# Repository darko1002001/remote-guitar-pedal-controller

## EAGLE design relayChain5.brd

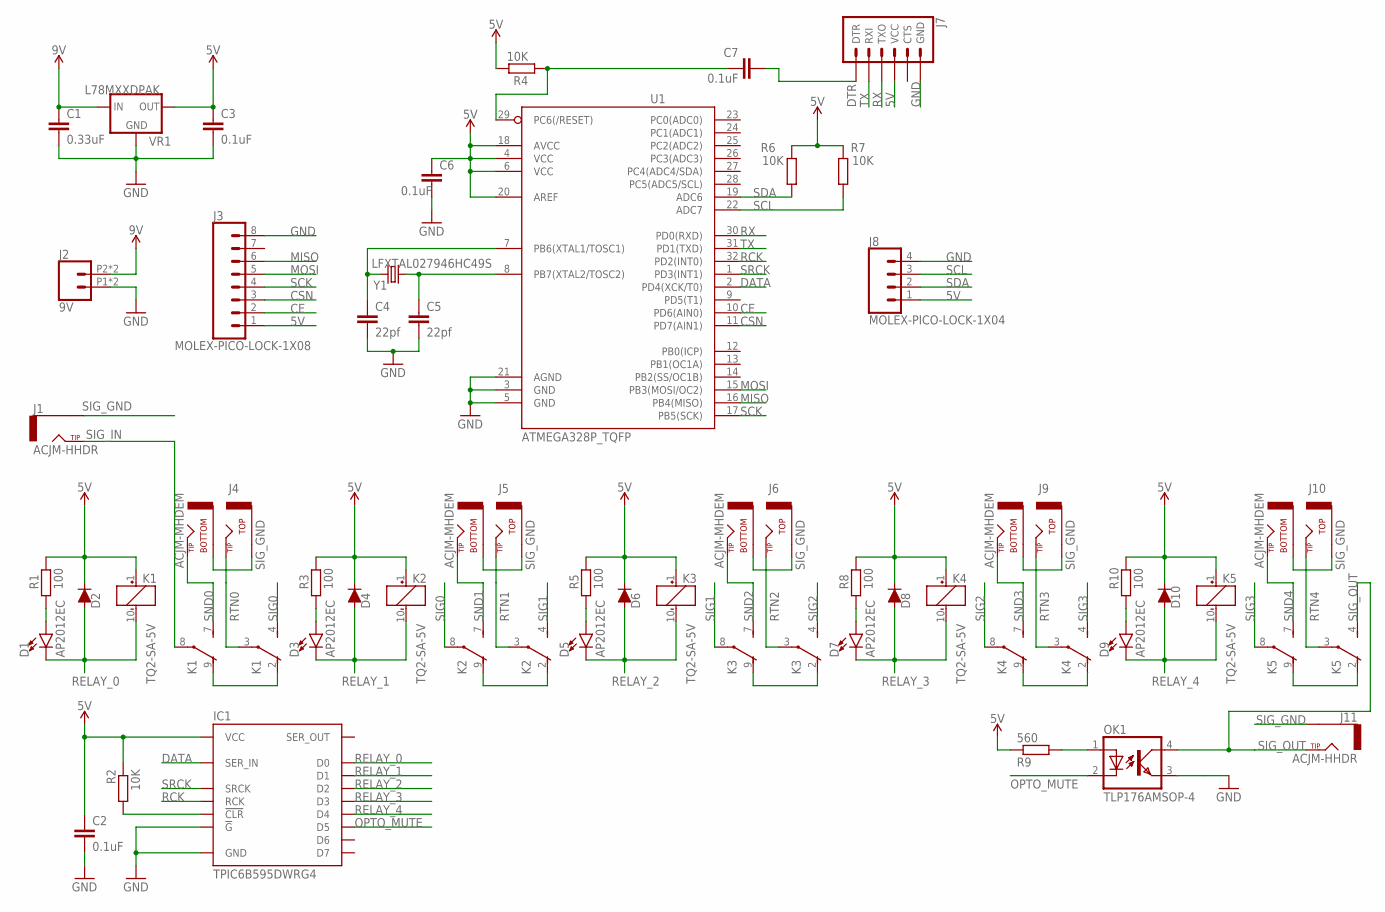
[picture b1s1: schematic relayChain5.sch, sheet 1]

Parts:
C1: 0.33uF; C0805
C2, C3, C6, C7: 0.1uF; C0805
C4, C5: 22pf; C0805
D1, D3, D5, D7, D9: AP2012EC; 0805-LED-AP2012EC
D2, D4, D6, D8, D10: 1n4148; SOD-123_MINI-SMA
IC1: TPIC6B595DWRG4; SOIC127P1032X265-20
J1, J11: ACJM-HHDR
J2: 9V; 1X02_POKEHOME
J3: MOLEX-PICO-LOCK-1X08
J4, J5, J6, J9, J10: ACJM-MHDEM
J7: 6_PIN_SERIAL_TARGETPTH-KIT; 1X06-KIT
J8: MOLEX-PICO-LOCK-1X04
K1, K2, K3, K4, K5: TQ2-SA-5V; TQ-SA
OK1: TLP176AMSOP-4; SOP254P715X220-4
R1, R3, R5, R8, R10: 100; M2012
R2: 10K; R0805
R4, R6, R7: 10K; M2012
R9: 560; R0805
U1: ATMEGA328P_TQFP; TQFP32-08
VR1: L78MXXDPAK; TO457P972X240-3
Y1: LFXTAL027946HC49S; XTAL1150X490X450

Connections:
5V: C2.1, C3.1, C6.1, D2.C, D4.C, D6.C, D8.C, D10.C, IC1.2 (VCC), J3.1, J7.4 (VCC), J8.1, K1.1 (+), K2.1 (+), K3.1 (+), K4.1 (+), K5.1 (+), R1.2, R2.1, R3.2, R4.2, R5.2, R6.1, R7.1, R8.2, R9.1, R10.2, U1.4 (VCC), U1.6 (VCC), U1.18 (AVCC), U1.20 (AREF), VR1.2 (OUT)
9V: C1.1, J2.P2 (2), J2.P4 (2), VR1.1 (IN)
CE: J3.2, U1.10 (PD6(AIN0))
CSN: J3.3, U1.11 (PD7(AIN1))
DATA: IC1.3 (SER_IN), U1.2 (PD4(XCK/T0))
DTR: C7.2, J7.1 (DTR)
GND: C1.2, C2.2, C3.2, C4.2, C5.2, C6.2, IC1.9 (!G), IC1.10 (GND), IC1.11 (GND), IC1.19 (GND), J2.P1 (1), J2.P3 (1), J3.8, J7.6 (GND), J8.4, OK1.3 (EMIT), U1.3 (GND), U1.5 (GND), U1.21 (AGND), VR1.3 (GND)
MISO: J3.6, U1.16 (PB4(MISO))
MOSI: J3.5, U1.15 (PB3(MOSI/OC2))
unnamed: K1.2 (O), K1.9 (O)
unnamed: IC1.8 (!CLR), R2.2
unnamed: D1.A, R1.1
unnamed: K2.2 (O), K2.9 (O)
unnamed: D3.A, R3.1
unnamed: K3.2 (O), K3.9 (O)
unnamed: D5.A, R5.1
unnamed: K4.2 (O), K4.9 (O)
unnamed: D7.A, R8.1
unnamed: K5.2 (O), K5.9 (O)
unnamed: D9.A, R10.1
unnamed: OK1.1 (A), R9.2
unnamed: C4.1, U1.7 (PB6(XTAL1/TOSC1)), Y1.1
unnamed: C5.1, U1.8 (PB7(XTAL2/TOSC2)), Y1.2
unnamed: C7.1, R4.1, U1.29 (PC6(/RESET))
OPTO_MUTE: IC1.15 (D5), OK1.2 (C)
RCK: IC1.12 (RCK), U1.32 (PD2(INT0))
RELAY_0: D1.C, D2.A, IC1.4 (D0), K1.10 (-)
RELAY_1: D3.C, D4.A, IC1.5 (D1), K2.10 (-)
RELAY_2: D5.C, D6.A, IC1.6 (D2), K3.10 (-)
RELAY_3: D7.C, D8.A, IC1.7 (D3), K4.10 (-)
RELAY_4: D9.C, D10.A, IC1.14 (D4), K5.10 (-)
RTN0: J4.9 (TIP_TOP), J4.12 (TIP_TOP), K1.3
RTN1: J5.9 (TIP_TOP), J5.12 (TIP_TOP), K2.3
RTN2: J6.9 (TIP_TOP), J6.12 (TIP_TOP), K3.3
RTN3: J9.9 (TIP_TOP), J9.12 (TIP_TOP), K4.3
RTN4: J10.9 (TIP_TOP), J10.12 (TIP_TOP), K5.3
RX: J7.3 (TXO), U1.30 (PD0(RXD))
SCK: J3.4, U1.17 (PB5(SCK))
SCL: J8.3, R7.2, U1.22 (ADC7)
SDA: J8.2, R6.2, U1.19 (ADC6)
SIG0: K1.4 (S), K2.8
SIG1: K2.4 (S), K3.8
SIG2: K3.4 (S), K4.8
SIG3: K4.4 (S), K5.8
SIG_GND: J1.SLEEVE_1 (SLEEVE), J1.SLEEVE_2 (SLEEVE), J4.1 (SLEEVE_BOTTOM), J4.4 (SLEEVE_BOTTOM), J4.7 (SLEEVE_TOP), J4.10 (SLEEVE_TOP), J5.1 (SLEEVE_BOTTOM), J5.4 (SLEEVE_BOTTOM), J5.7 (SLEEVE_TOP), J5.10 (SLEEVE_TOP), J6.1 (SLEEVE_BOTTOM), J6.4 (SLEEVE_BOTTOM), J6.7 (SLEEVE_TOP), J6.10 (SLEEVE_TOP), J9.1 (SLEEVE_BOTTOM), J9.4 (SLEEVE_BOTTOM), J9.7 (SLEEVE_TOP), J9.10 (SLEEVE_TOP), J10.1 (SLEEVE_BOTTOM), J10.4 (SLEEVE_BOTTOM), J10.7 (SLEEVE_TOP), J10.10 (SLEEVE_TOP), J11.SLEEVE_1 (SLEEVE), J11.SLEEVE_2 (SLEEVE)
SIG_IN: J1.TIP_1 (TIP), J1.TIP_2 (TIP), K1.8
SIG_OUT: J11.TIP_1 (TIP), J11.TIP_2 (TIP), K5.4 (S), OK1.4 (COL)
SND0: J4.3 (TIP_BOTTOM), J4.6 (TIP_BOTTOM), K1.7 (S)
SND1: J5.3 (TIP_BOTTOM), J5.6 (TIP_BOTTOM), K2.7 (S)
SND2: J6.3 (TIP_BOTTOM), J6.6 (TIP_BOTTOM), K3.7 (S)
SND3: J9.3 (TIP_BOTTOM), J9.6 (TIP_BOTTOM), K4.7 (S)
SND4: J10.3 (TIP_BOTTOM), J10.6 (TIP_BOTTOM), K5.7 (S)
SRCK: IC1.13 (SRCK), U1.1 (PD3(INT1))
TX: J7.2 (RXI), U1.31 (PD1(TXD))

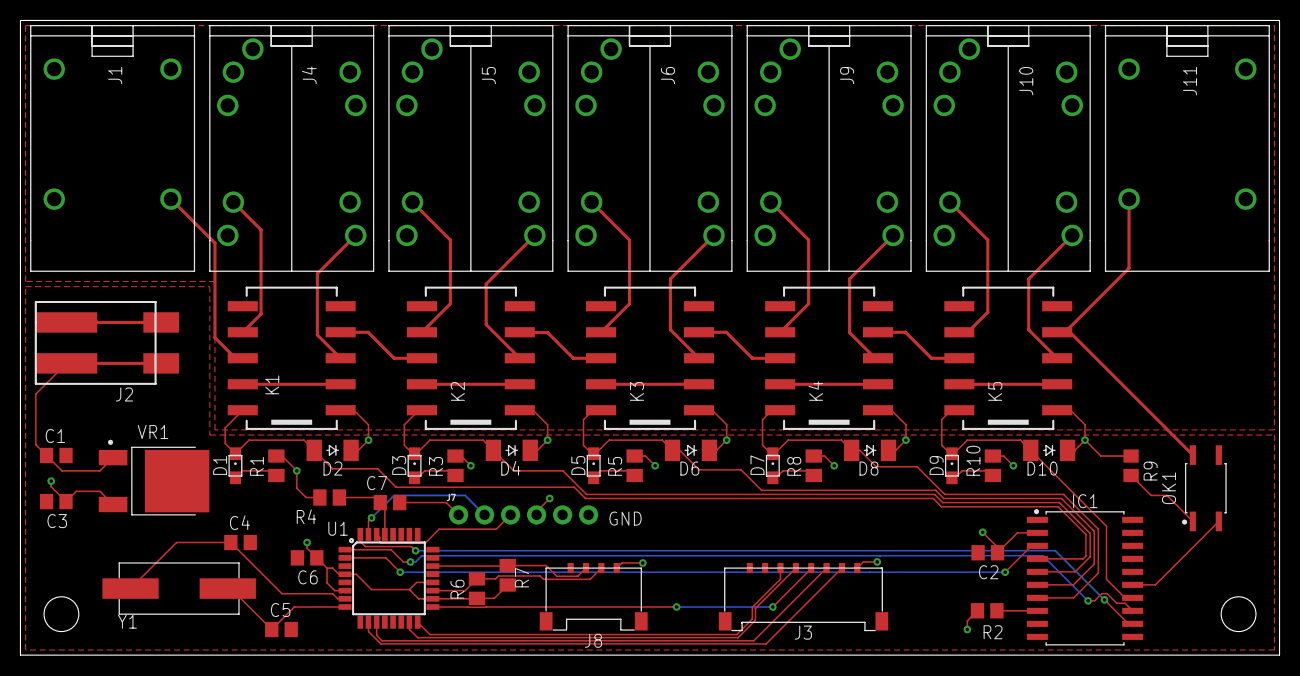
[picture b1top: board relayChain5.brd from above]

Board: 2 copper layers, 123.0 x 62.0 mm, 48 parts (0 on the bottom side), 54 nets.

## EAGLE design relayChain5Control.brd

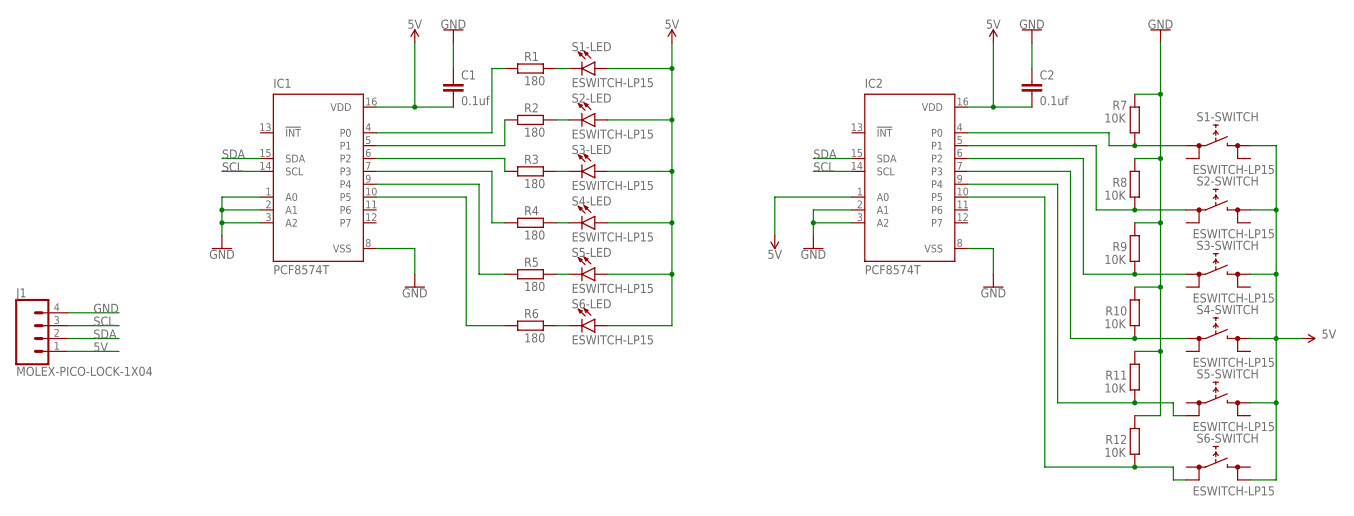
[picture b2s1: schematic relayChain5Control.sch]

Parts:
C1, C2: 0.1uf; C0805
IC1, IC2: PCF8574T; SO16W
J1: MOLEX-PICO-LOCK-1X04
R1, R2, R3, R4, R5, R6: 180; R2012
R7, R8, R9, R10, R11, R12: 10K; R2012
S1, S2, S3, S4, S5, S6: ESWITCH-LP15

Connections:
5V: C1.2, C2.2, IC1.16 (VDD), IC2.1 (A0), IC2.16 (VDD), J1.1, S1.P$3 (1), S1.P$5 (A), S2.P$3 (1), S2.P$5 (A), S3.P$3 (1), S3.P$5 (A), S4.P$3 (1), S4.P$5 (A), S5.P$3 (1), S5.P$5 (A), S6.P$4 (1), S6.P$5 (A)
GND: C1.1, C2.1, IC1.1 (A0), IC1.2 (A1), IC1.3 (A2), IC1.8 (VSS), IC2.2 (A1), IC2.3 (A2), IC2.8 (VSS), J1.4, R7.2, R8.2, R9.2, R10.2, R11.2, R12.2
unnamed: IC1.4 (P0), R1.1
unnamed: R1.2, S1.P$6 (C)
unnamed: IC1.5 (P1), R2.1
unnamed: IC1.6 (P2), R3.1
unnamed: IC2.4 (P0), R7.1, S1.P$1 (0)
unnamed: IC2.5 (P1), R8.1, S2.P$1 (0)
unnamed: R2.2, S2.P$6 (C)
unnamed: IC2.6 (P2), R9.1, S3.P$1 (0)
unnamed: IC2.7 (P3), R10.1, S4.P$1 (0)
unnamed: IC2.9 (P4), R11.1, S5.P$2 (0)
unnamed: IC1.7 (P3), R4.1
unnamed: IC1.9 (P4), R5.1
unnamed: R3.2, S3.P$6 (C)
unnamed: IC2.10 (P5), R12.1, S6.P$2 (0)
unnamed: R4.2, S4.P$6 (C)
unnamed: R5.2, S5.P$6 (C)
unnamed: R6.2, S6.P$6 (C)
unnamed: IC1.10 (P5), R6.1
SCL: IC1.14 (SCL), IC2.14 (SCL), J1.3
SDA: IC1.15 (SDA), IC2.15 (SDA), J1.2

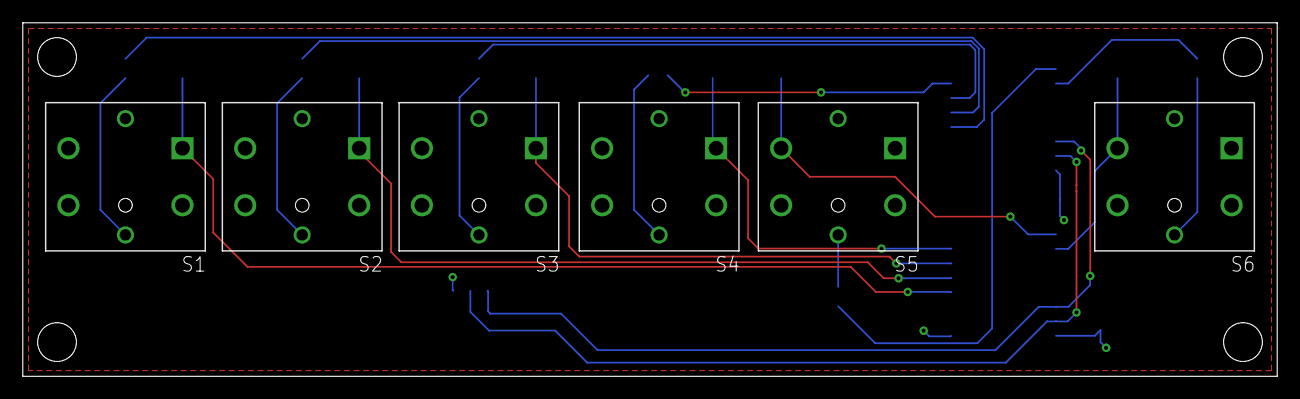
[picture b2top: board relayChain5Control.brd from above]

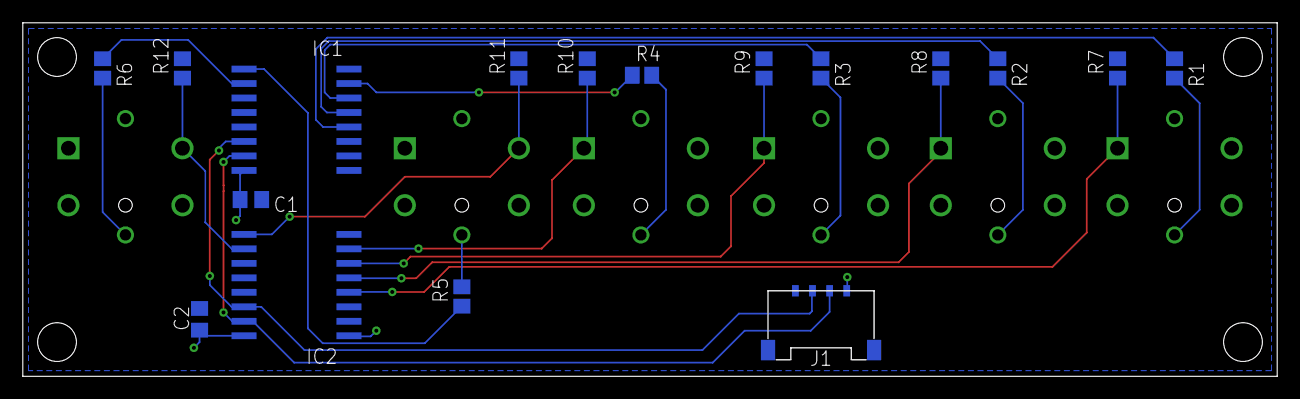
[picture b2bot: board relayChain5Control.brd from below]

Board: 2 copper layers, 110.0 x 31.0 mm, 23 parts (17 on the bottom side), 22 nets.

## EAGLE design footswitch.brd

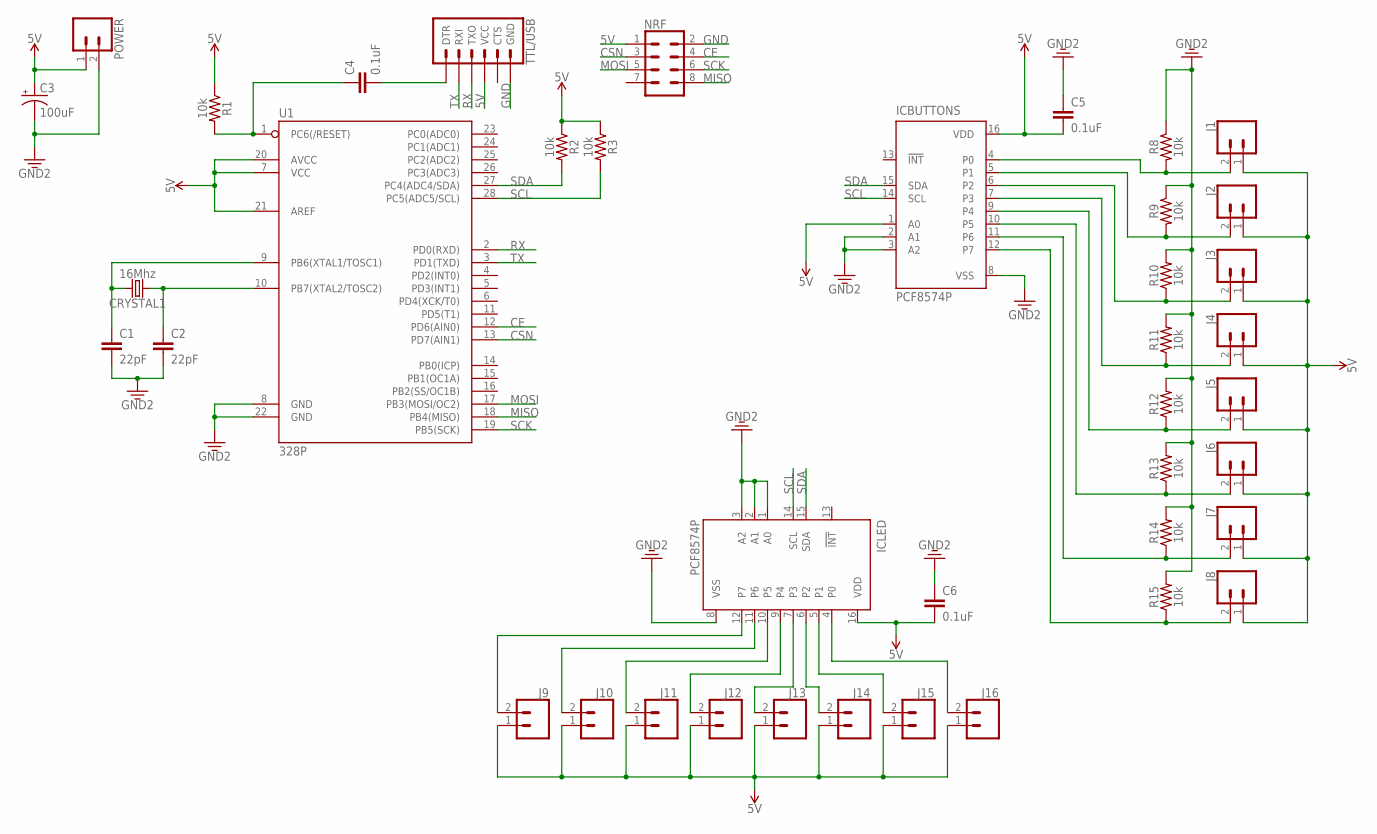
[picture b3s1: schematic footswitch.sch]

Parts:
C1, C2: 22pF; CAP-PTH-2.54
C3: 100uF; CPOL-RADIAL-2.5MM-6.5MM
C4, C5, C6: 0.1uF; CAP-PTH-SMALL-KIT
CRYSTAL1: 16Mhz; HC49US
ICBUTTONS: PCF8574P; DIL16
ICLED: PCF8574P; DIL16
J1, J2, J3, J4, J5, J6, J7, J8, J9, J10, J11, J12, J13, J14, J15, J16: CONN_02POLAR; MOLEX-1X2
NRF: CONN_04X2; 2X4
POWER: CONN_02; 1X02
R1, R2, R3, R8, R9, R10, R11, R12, R13, R14, R15: 10k; AXIAL-0.3
TTL/USB: 6_PIN_SERIAL_TARGETPTH-KIT; 1X06-KIT
U1: 328P; DIP28

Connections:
5V: C3.1 (+), C5.2, C6.2, ICBUTTONS.1 (A0), ICBUTTONS.16 (VDD), ICLED.16 (VDD), J1.1, J2.1, J3.1, J4.1, J5.1, J6.1, J7.1, J8.1, J9.1, J10.1, J11.1, J12.1, J13.1, J14.1, J15.1, J16.1, NRF.1, POWER.1, R1.P$1 (1), R2.P$1 (1), R3.P$1 (1), TTL/USB.4 (VCC), U1.7 (VCC), U1.20 (AVCC), U1.21 (AREF)
CE: NRF.4, U1.12 (PD6(AIN0))
CSN: NRF.3, U1.13 (PD7(AIN1))
GND: C1.2, C2.2, C3.2 (-), C5.1, C6.1, ICBUTTONS.2 (A1), ICBUTTONS.3 (A2), ICBUTTONS.8 (VSS), ICLED.1 (A0), ICLED.2 (A1), ICLED.3 (A2), ICLED.8 (VSS), NRF.2, POWER.2, R8.P$1 (1), R9.P$1 (1), R10.P$2 (2), R11.P$2 (2), R12.P$2 (2), R13.P$2 (2), R14.P$2 (2), R15.P$2 (2), TTL/USB.6 (GND), U1.8 (GND), U1.22 (GND)
MISO: NRF.8, U1.18 (PB4(MISO))
MOSI: NRF.5, U1.17 (PB3(MOSI/OC2))
unnamed: C4.1, R1.P$2 (2), U1.1 (PC6(/RESET))
unnamed: C1.1, CRYSTAL1.2, U1.9 (PB6(XTAL1/TOSC1))
unnamed: C2.1, CRYSTAL1.1, U1.10 (PB7(XTAL2/TOSC2))
unnamed: C4.2, TTL/USB.1 (DTR)
unnamed: ICBUTTONS.4 (P0), J1.2, R8.P$2 (2)
unnamed: ICBUTTONS.5 (P1), J2.2, R9.P$2 (2)
unnamed: ICLED.7 (P3), J13.2
unnamed: ICBUTTONS.6 (P2), J3.2, R10.P$1 (1)
unnamed: ICBUTTONS.7 (P3), J4.2, R11.P$1 (1)
unnamed: ICBUTTONS.9 (P4), J5.2, R12.P$1 (1)
unnamed: ICBUTTONS.10 (P5), J6.2, R13.P$1 (1)
unnamed: ICBUTTONS.11 (P6), J7.2, R14.P$1 (1)
unnamed: ICBUTTONS.12 (P7), J8.2, R15.P$1 (1)
unnamed: ICLED.6 (P2), J14.2
unnamed: ICLED.12 (P7), J9.2
unnamed: ICLED.11 (P6), J10.2
unnamed: ICLED.10 (P5), J11.2
unnamed: ICLED.9 (P4), J12.2
unnamed: ICLED.5 (P1), J15.2
unnamed: ICLED.4 (P0), J16.2
RX: TTL/USB.3 (TXO), U1.2 (PD0(RXD))
SCK: NRF.6, U1.19 (PB5(SCK))
SCL: ICBUTTONS.14 (SCL), ICLED.14 (SCL), R3.P$2 (2), U1.28 (PC5(ADC5/SCL))
SDA: ICBUTTONS.15 (SDA), ICLED.15 (SDA), R2.P$2 (2), U1.27 (PC4(ADC4/SDA))
TX: TTL/USB.2 (RXI), U1.3 (PD1(TXD))

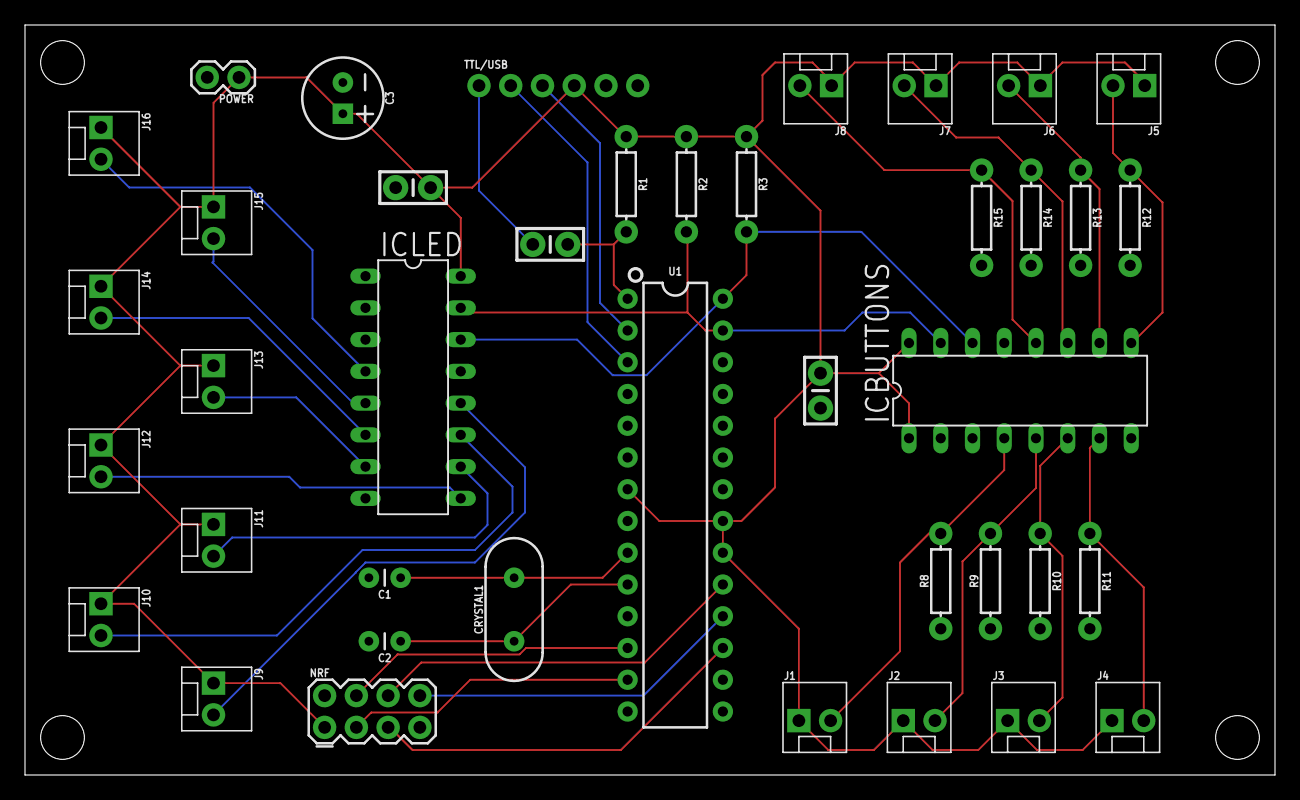
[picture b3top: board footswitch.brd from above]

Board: 2 copper layers, 100.0 x 60.0 mm, 40 parts (0 on the bottom side), 31 nets.

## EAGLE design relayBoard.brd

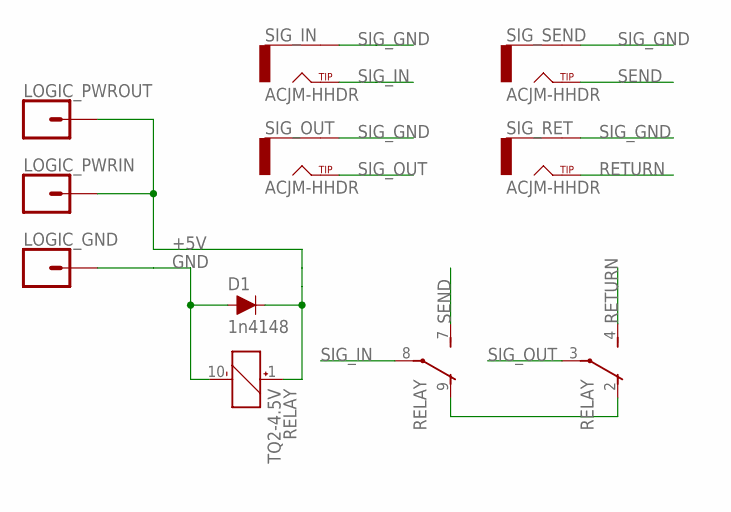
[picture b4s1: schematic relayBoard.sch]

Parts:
D1: 1n4148; DIODE-1N4148
LOGIC_GND: CONN_01; 1X01
LOGIC_PWRIN: CONN_01; 1X01
LOGIC_PWROUT: CONN_01; 1X01
RELAY: TQ2-4.5V; TQ2
SIG_IN: ACJM-HHDR
SIG_OUT: ACJM-HHDR
SIG_RET: ACJM-HHDR
SIG_SEND: ACJM-HHDR

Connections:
+5V: D1.C, LOGIC_PWRIN.1, LOGIC_PWROUT.1, RELAY.1 (+)
GND: D1.A, LOGIC_GND.1, RELAY.10 (-)
unnamed: RELAY.2 (O), RELAY.9 (O)
RETURN: RELAY.4 (S), SIG_RET.TIP_1 (TIP), SIG_RET.TIP_2 (TIP)
SEND: RELAY.7 (S), SIG_SEND.TIP_1 (TIP), SIG_SEND.TIP_2 (TIP)
SIG_GND: SIG_IN.SLEEVE_1 (SLEEVE), SIG_IN.SLEEVE_2 (SLEEVE), SIG_OUT.SLEEVE_1 (SLEEVE), SIG_OUT.SLEEVE_2 (SLEEVE), SIG_RET.SLEEVE_1 (SLEEVE), SIG_RET.SLEEVE_2 (SLEEVE), SIG_SEND.SLEEVE_1 (SLEEVE), SIG_SEND.SLEEVE_2 (SLEEVE)
SIG_IN: RELAY.8, SIG_IN.TIP_1 (TIP), SIG_IN.TIP_2 (TIP)
SIG_OUT: RELAY.3, SIG_OUT.TIP_1 (TIP), SIG_OUT.TIP_2 (TIP)

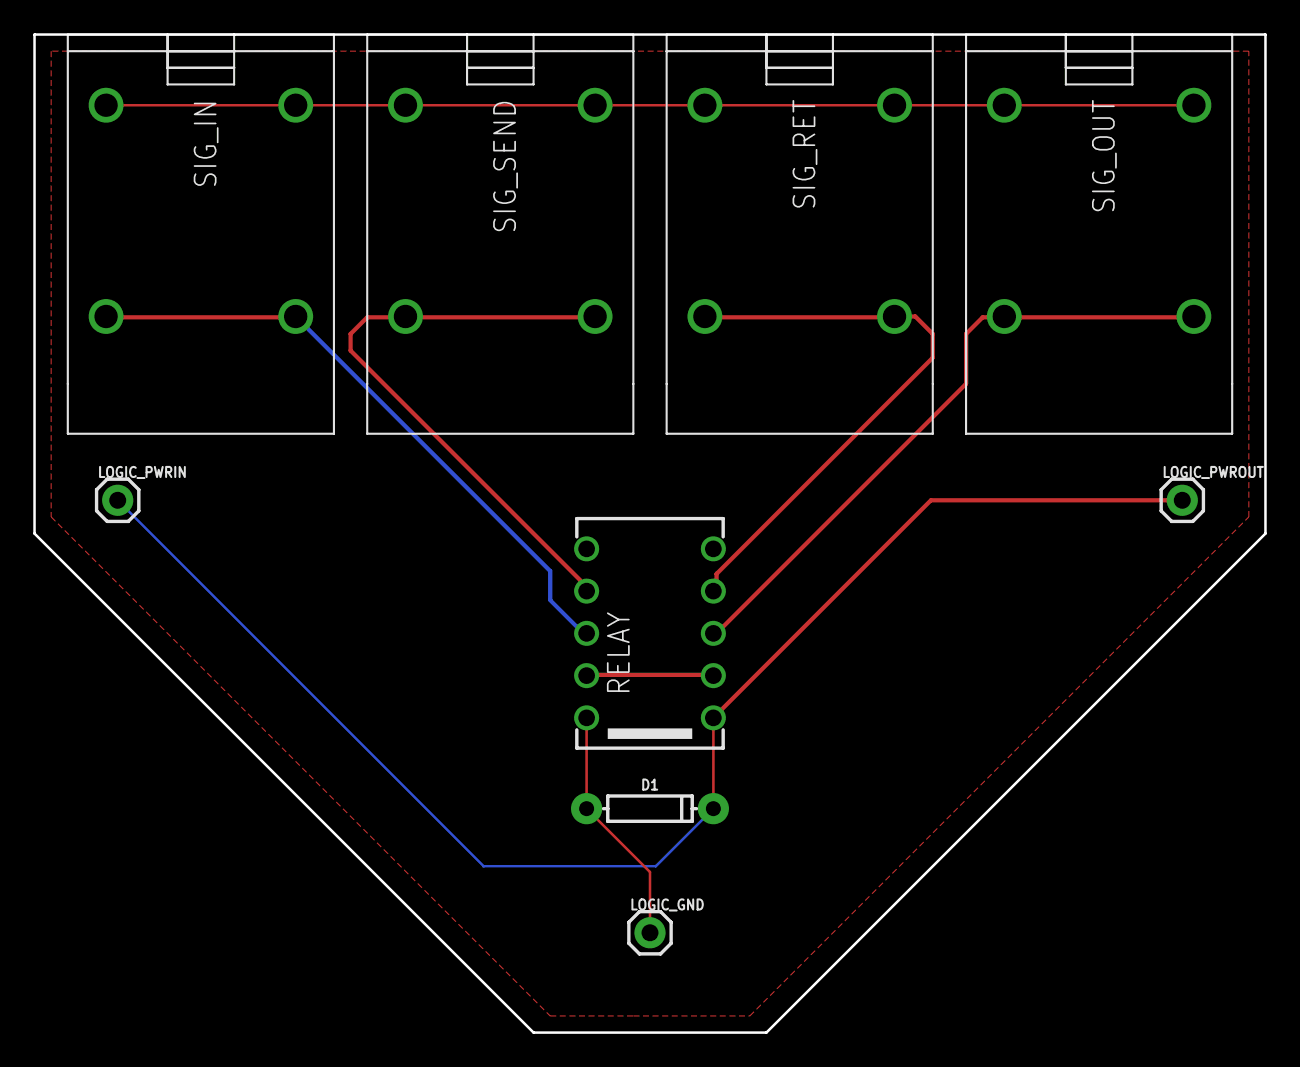
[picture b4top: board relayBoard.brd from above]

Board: 2 copper layers, 74.0 x 60.0 mm, 9 parts (0 on the bottom side), 8 nets.

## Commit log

2019-01-01 finished initial design

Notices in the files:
parts and their libraries:
SparkFun-Capacitors: Licensing: Creative Commons ShareAlike 4.0 International - https://creativecommons.org/licenses/by-sa/4.0
